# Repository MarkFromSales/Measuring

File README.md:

# Measuring
General stuff for measuring and etc. using PCBs

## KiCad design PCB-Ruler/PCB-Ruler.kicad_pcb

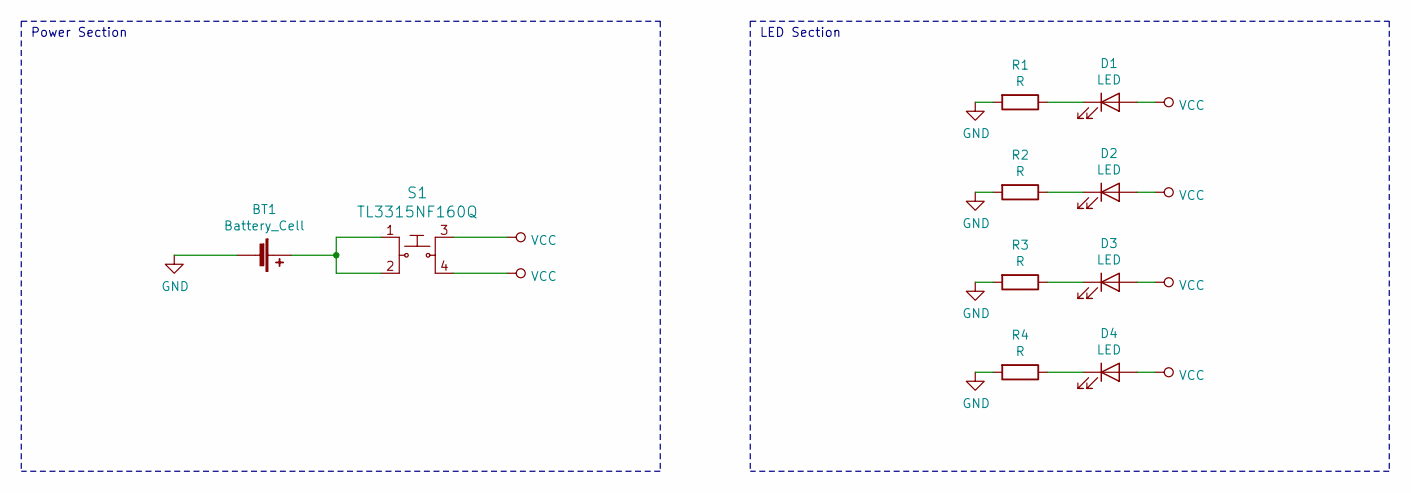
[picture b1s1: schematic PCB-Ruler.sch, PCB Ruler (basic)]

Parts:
BT1: Battery_Cell; BatteryHolder_MPD_BC2003_1x2032
D1, D2, D3, D4: LED; LED_0805_2012Metric_Pad1.15x1.40mm_HandSolder
R1, R2, R3, R4: R; R_0805_2012Metric_Pad1.15x1.40mm_HandSolder
S1: TL3315NF160Q; Switch_Tactile_SMD_4.5x4.5mm_TL3315NF160Q; MPN TL3315NF160Q; Digi-Key_PN EG4621CT-ND

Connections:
GND: BT1.2 (-), R1.2, R2.2, R3.2, R4.2
unnamed: BT1.1 (+), S1.1, S1.2
unnamed: D1.1 (K), R1.1
unnamed: D2.1 (K), R2.1
unnamed: D3.1 (K), R3.1
unnamed: D4.1 (K), R4.1
VCC: D1.2 (A), D2.2 (A), D3.2 (A), D4.2 (A), S1.3, S1.4

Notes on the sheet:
Power Section
LED Section

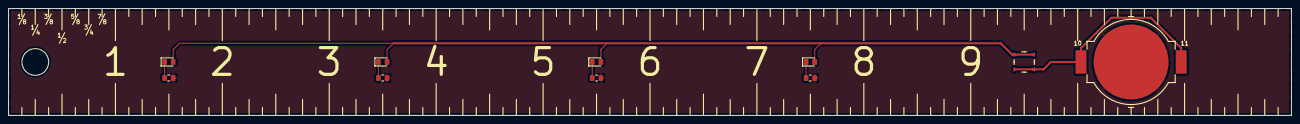
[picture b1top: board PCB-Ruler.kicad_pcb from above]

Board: 2 copper layers, 304.8 x 25.4 mm, 10 parts (0 on the bottom side), 7 nets.

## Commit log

2020-04-19 Initial
